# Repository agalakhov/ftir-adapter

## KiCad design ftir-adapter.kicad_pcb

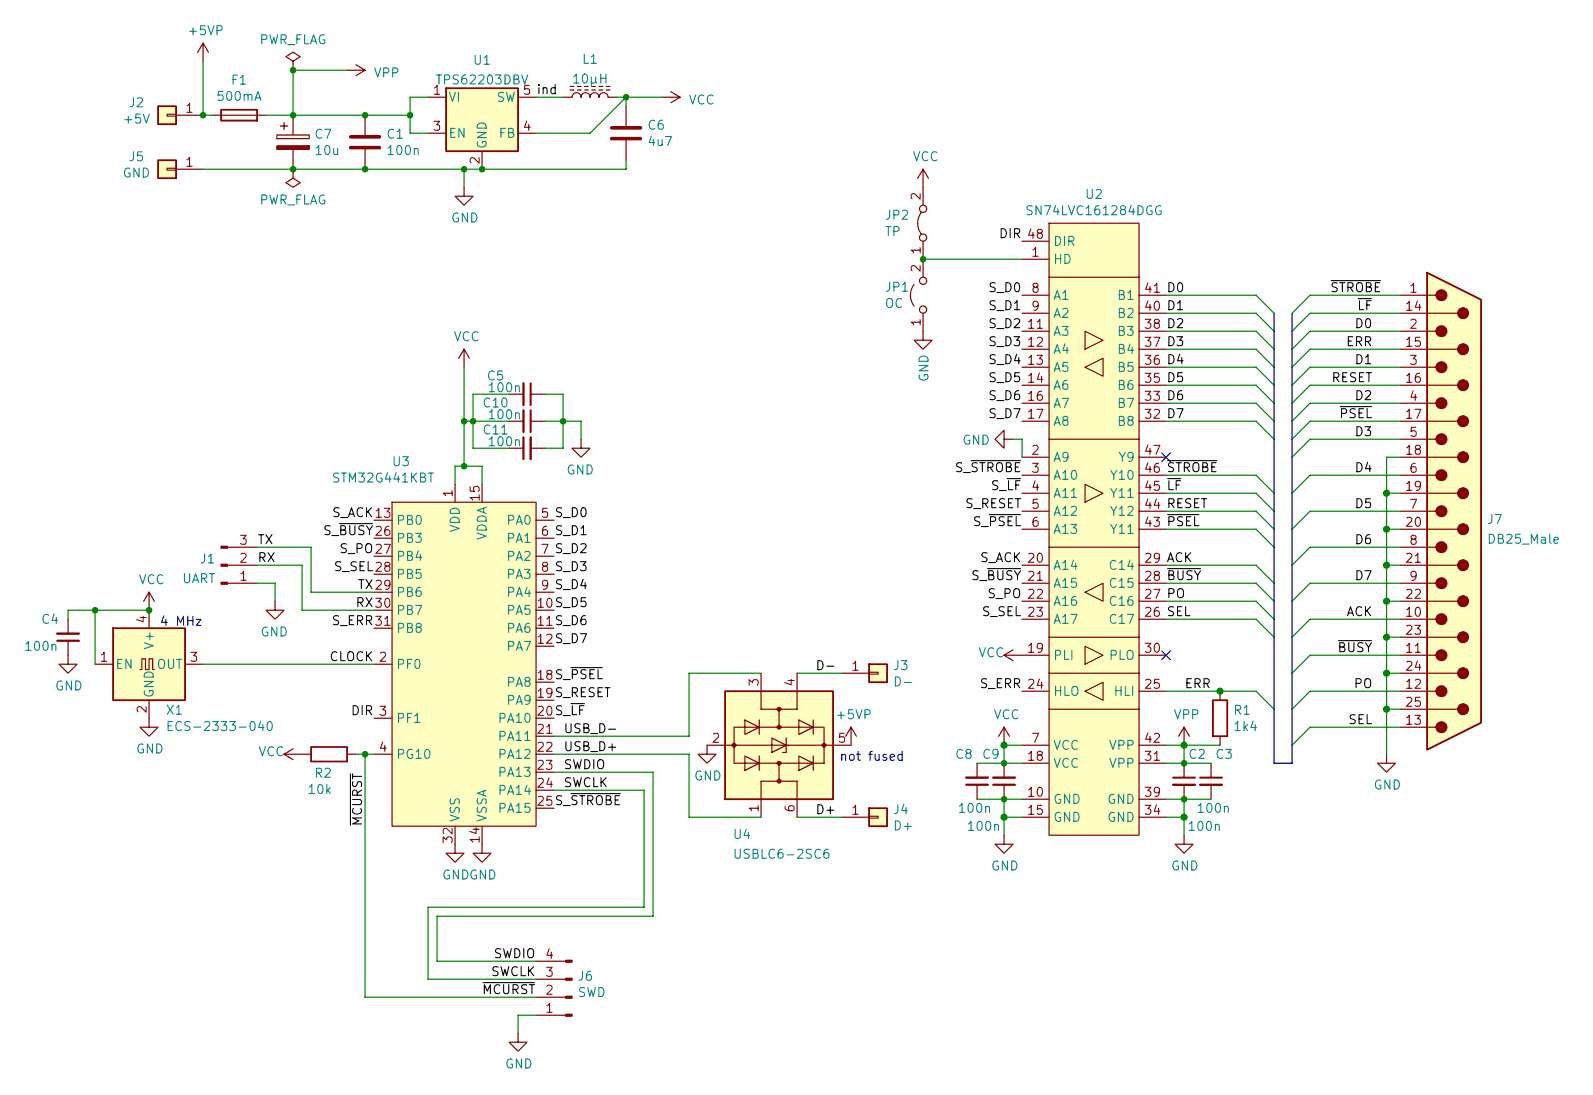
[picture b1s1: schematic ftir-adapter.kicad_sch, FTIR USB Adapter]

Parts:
C1: 100n; C_0805_2012Metric_Pad1.18x1.45mm_HandSolder
C2, C3, C4, C5, C8, C9, C10, C11: 100n; C_0603_1608Metric_Pad1.08x0.95mm_HandSolder
C6: 4u7; C_0805_2012Metric_Pad1.18x1.45mm_HandSolder
C7: 10u; CP_Elec_4x3
F1: 500mA; Fuse_0805_2012Metric_Pad1.15x1.40mm_HandSolder
J1: UART; PinHeader_1x03_P1.27mm_Vertical
J2: +5V; SolderWire-0.15sqmm_1x01_D0.5mm_OD1.5mm
J3: D-; SolderWire-0.15sqmm_1x01_D0.5mm_OD1.5mm
J4: D+; SolderWire-0.15sqmm_1x01_D0.5mm_OD1.5mm
J5: GND; SolderWire-0.15sqmm_1x01_D0.5mm_OD1.5mm
J6: SWD; PinHeader_1x04_P1.27mm_Vertical
J7: DB25_Male; DSUB-25_Male_EdgeMount_P2.77mm
JP1: OC; R_0805_2012Metric_Pad1.20x1.40mm_HandSolder
JP2: TP; R_0805_2012Metric_Pad1.20x1.40mm_HandSolder
L1: 10µH; L_Coilcraft_XxL4030
R1: 1k4; R_0603_1608Metric_Pad0.98x0.95mm_HandSolder
R2: 10k; R_0603_1608Metric_Pad0.98x0.95mm_HandSolder
U1: TPS62203DBV; SOT-23-5
U2: SN74LVC161284DGG; TSSOP-48_6.1x12.5mm_P0.5mm
U3: STM32G441KBT; LQFP-32_7x7mm_P0.8mm
U4: USBLC6-2SC6; SOT-23-6
X1: ECS-2333-040; Oscillator_SMD_EuroQuartz_XO32-4Pin_3.2x2.5mm

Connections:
+5VP: F1.1, J2.1, U4.5 (VBUS)
/ACK: J7.10, U2.29 (C14)
/CLOCK: U3.2 (PF0), X1.3 (OUT)
/D0: J7.2, U2.41 (B1)
/D1: J7.3, U2.40 (B2)
/D2: J7.4, U2.38 (B3)
/D3: J7.5, U2.37 (B4)
/D4: J7.6, U2.36 (B5)
/D5: J7.7, U2.35 (B6)
/D6: J7.8, U2.33 (B7)
/D7: J7.9, U2.32 (B8)
/D+: J4.1, U4.6 (I/O1)
/D-: J3.1, U4.4 (I/O2)
/DIR: U2.48 (DIR), U3.3 (PF1)
/ERR: J7.15, R1.1, U2.25 (HLI)
/PO: J7.12, U2.27 (C16)
/RESET: J7.16, U2.44 (Y12)
/RX: J1.2, U3.30 (PB7)
/SEL: J7.13, U2.26 (C17)
/SWCLK: J6.3, U3.24 (PA14)
/SWDIO: J6.4, U3.23 (PA13)
/S_ACK: U2.20 (A14), U3.13 (PB0)
/S_D0: U2.8 (A1), U3.5 (PA0)
/S_D1: U2.9 (A2), U3.6 (PA1)
/S_D2: U2.11 (A3), U3.7 (PA2)
/S_D3: U2.12 (A4), U3.8 (PA3)
/S_D4: U2.13 (A5), U3.9 (PA4)
/S_D5: U2.14 (A6), U3.10 (PA5)
/S_D6: U2.16 (A7), U3.11 (PA6)
/S_D7: U2.17 (A8), U3.12 (PA7)
/S_ERR: U2.24 (HLO), U3.31 (PB8)
/S_PO: U2.22 (A16), U3.27 (PB4)
/S_RESET: U2.5 (A12), U3.19 (PA9)
/S_SEL: U2.23 (A17), U3.28 (PB5)
/S_~BUSY: U2.21 (A15), U3.26 (PB3)
/S_~LF: U2.4 (A11), U3.20 (PA10)
/S_~PSEL: U2.6 (A13), U3.18 (PA8)
/S_~STROBE: U2.3 (A10), U3.25 (PA15)
/TX: J1.3, U3.29 (PB6)
/USB_D+: U3.22 (PA12), U4.1 (I/O1)
/USB_D-: U3.21 (PA11), U4.3 (I/O2)
/ind: L1.1, U1.5 (SW)
/~BUSY: J7.11, U2.28 (C15)
/~LF: J7.14, U2.45 (Y11)
/~MCURST: J6.2, R2.2, U3.4 (PG10)
/~PSEL: J7.17, U2.43 (Y11)
/~STROBE: J7.1, U2.46 (Y10)
GND: C1.2, C2.2, C3.2, C4.1, C5.1, C6.2, C7.2, C8.1, C9.1, C10.1, C11.2, J1.1, J5.1, J6.1, J7.18, J7.19, J7.20, J7.21, J7.22, J7.23, J7.24, J7.25, JP1.1 (A), U1.2 (GND), U2.2 (A9), U2.10 (GND), U2.15 (GND), U2.34 (GND), U2.39 (GND), U3.14 (VSSA), U3.16 (VSS), U3.32 (VSS), U4.2 (GND), X1.2 (GND)
unnamed: JP1.2 (B), JP2.1 (A), U2.1 (HD)
VCC: C4.2, C5.2, C6.1, C8.2, C9.2, C10.2, C11.1, JP2.2 (B), L1.2, R2.1, U1.4 (FB), U2.7 (VCC), U2.18 (VCC), U2.19 (PLI), U3.1 (VDD), U3.15 (VDDA), U3.17 (VDD), X1.1 (EN), X1.4 (V+)
VPP: C1.1, C2.1, C3.1, C7.1, F1.2, R1.2, U1.1 (VI), U1.3 (EN), U2.31 (VPP), U2.42 (VPP)

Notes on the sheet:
4 MHz
not fused

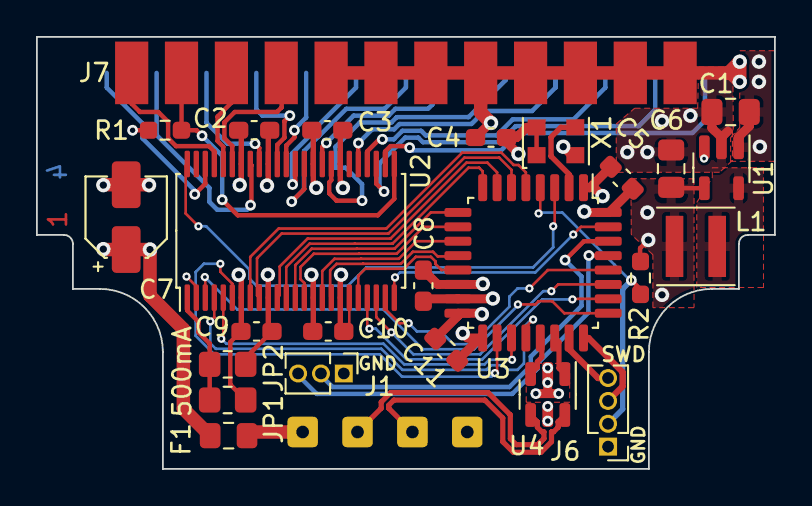
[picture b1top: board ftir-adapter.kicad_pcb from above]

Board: 4 copper layers, 41.0 x 24.0 mm, 29 parts (1 on the bottom side), 51 nets.

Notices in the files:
ftir-adapter.kicad_pcb:
©2022 Alexey Galakhov
